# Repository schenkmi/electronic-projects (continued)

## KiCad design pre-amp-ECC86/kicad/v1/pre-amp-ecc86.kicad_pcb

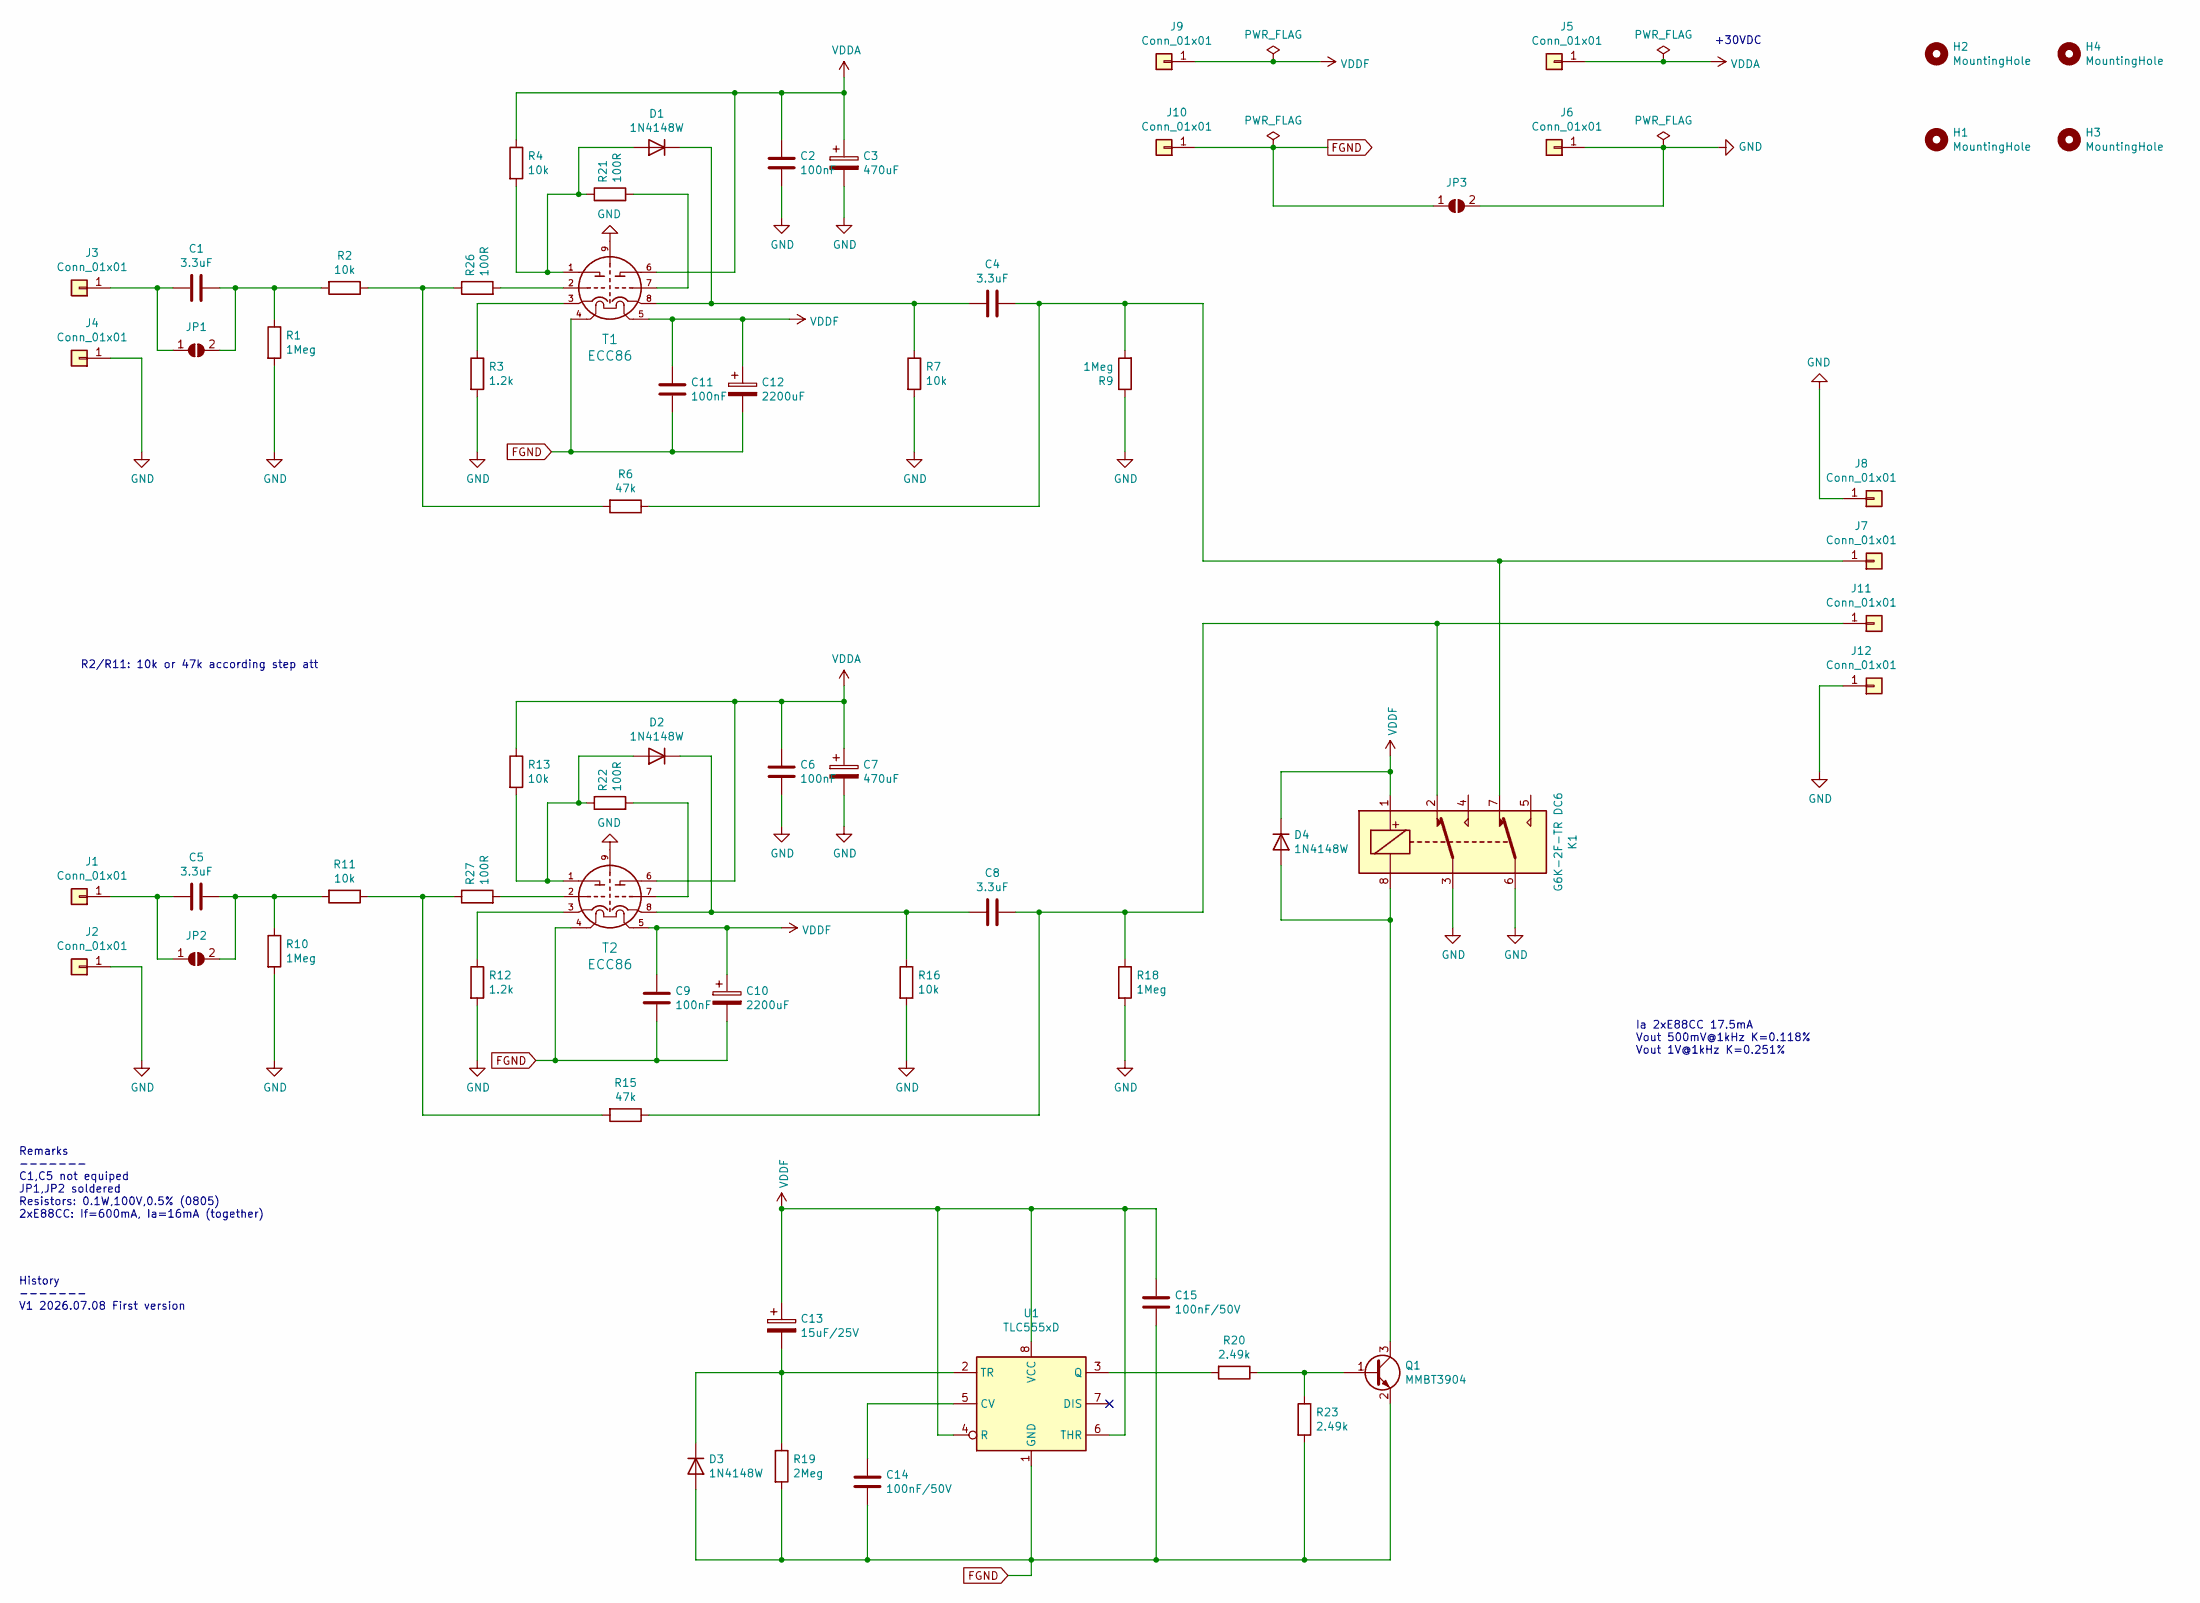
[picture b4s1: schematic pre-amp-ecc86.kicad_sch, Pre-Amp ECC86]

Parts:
C1, C4, C5, C8: 3.3uF; C_Rect_L7.2mm_W7.2mm_P5.00mm_FKS2_FKP2_MKS2_MKP2
C2, C6, C9, C11: 100nF; C_1206_3216Metric_Pad1.33x1.80mm_HandSolder
C3, C7: 470uF; CP_Radial_D12.5mm_P5.00mm
C10, C12: 2200uF; CP_Radial_D16.0mm_P7.50mm
C13: 15uF/25V; CP_EIA-3216-12_Kemet-S_HandSolder
C14, C15: 100nF/50V; C_0805_2012Metric_Pad1.18x1.45mm_HandSolder
D1, D2, D3, D4: 1N4148W; D_SOD-123
H1, H2, H3, H4: MountingHole; MountingHole_3.2mm_M3_Pad_Via
J1, J2, J3, J4, J7, J8, J11, J12: Conn_01x01; Pin_D1.0mm_L10.0mm
J5, J6, J9, J10: Conn_01x01; Pin_D1.3mm_L11.0mm
JP1, JP2, JP3: SolderJumper_2_Open; SolderJumper-2_P1.3mm_Open_Pad1.0x1.5mm
K1: G6K-2F-TR DC6; Relay_DPDT_Omron_G6K-2F
Q1: MMBT3904; SOT-23
R1, R9, R10, R18: 1Meg; R_0805_2012Metric_Pad1.20x1.40mm_HandSolder
R2, R4, R7, R11, R13, R16: 10k; R_0805_2012Metric_Pad1.20x1.40mm_HandSolder
R3, R12: 1.2k; R_0805_2012Metric_Pad1.20x1.40mm_HandSolder
R6, R15: 47k; R_0805_2012Metric_Pad1.20x1.40mm_HandSolder
R19: 2Meg; R_0805_2012Metric_Pad1.20x1.40mm_HandSolder
R20, R23: 2.49k; R_0805_2012Metric_Pad1.20x1.40mm_HandSolder
R21, R22, R26, R27: 100R; R_0805_2012Metric_Pad1.20x1.40mm_HandSolder
T1, T2: ECC86; TubeNoval-ECC86
U1: TLC555xD; SOIC-8_3.9x4.9mm_P1.27mm

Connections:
FGND: C9.2, C10.2, C11.2, C12.2, C14.2, C15.2, D3.2 (A), J10.1 (Pin_1_1), JP3.1 (A), Q1.2 (E), R19.2, R23.2, T1.4 (h), T2.4 (h), U1.1 (GND)
GND: C2.2, C3.2, C6.2, C7.2, J2.1 (Pin_1_1), J4.1 (Pin_1_1), J6.1 (Pin_1_1), J8.1 (Pin_1_1), J12.1 (Pin_1_1), JP3.2 (B), K1.3, K1.6, R1.2, R3.2, R7.2, R9.1, R10.2, R12.2, R16.2, R18.2, T1.9 (s), T2.9 (s)
unnamed: D1.2 (A), R4.2, R21.1, T1.1 (qT1)
unnamed: C4.2, D1.1 (K), R7.1, T1.8 (kT2)
unnamed: D2.2 (A), R13.2, R22.1, T2.1 (qT1)
unnamed: C8.2, D2.1 (K), R16.1, T2.8 (kT2)
unnamed: C13.2, D3.1 (K), R19.1, U1.2 (TR)
unnamed: D4.2 (A), K1.8, Q1.3 (C)
unnamed: C5.2, J1.1 (Pin_1_1), JP2.1 (A)
unnamed: C1.2, J3.1 (Pin_1_1), JP1.1 (A)
unnamed: C4.1, J7.1 (Pin_1_1), K1.7, R6.1, R9.2
unnamed: C8.1, J11.1 (Pin_1_1), K1.2, R15.1, R18.1
unnamed: C1.1, JP1.2 (B), R1.1, R2.2
unnamed: C5.1, JP2.2 (B), R10.1, R11.2
unnamed: Q1.1 (B), R20.1, R23.1
unnamed: R2.1, R6.2, R26.1
unnamed: R11.1, R15.2, R27.1
unnamed: R26.2, T1.2 (gT1)
unnamed: R21.2, T1.7 (gT2)
unnamed: R3.1, T1.3 (kT1)
unnamed: R27.2, T2.2 (gT1)
unnamed: R22.2, T2.7 (gT2)
unnamed: R12.1, T2.3 (kT1)
unnamed: C14.1, U1.5 (CV)
unnamed: R20.2, U1.3 (Q)
VDDA: C2.1, C3.1, C6.1, C7.1, J5.1 (Pin_1_1), R4.1, R13.1, T1.6 (qT2), T2.6 (qT2)
VDDF: C9.1, C10.1, C11.1, C12.1, C13.1, C15.1, D4.1 (K), J9.1 (Pin_1_1), K1.1, T1.5 (h), T2.5 (h), U1.4 (R), U1.6 (THR), U1.8 (VCC)

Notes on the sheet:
Remarks ------- C1,C5 not equiped JP1,JP2 soldered Resistors: 0.1W,100V,0.5% (0805) 2xE88CC: If=600mA, Ia=16mA (together)
R2/R11: 10k or 47k according step att
Ia 2xE88CC 17.5mA Vout 500mV@1kHz K=0.118% Vout 1V@1kHz K=0.251%
History ------- V1 2026.07.08 First version
+30VDC

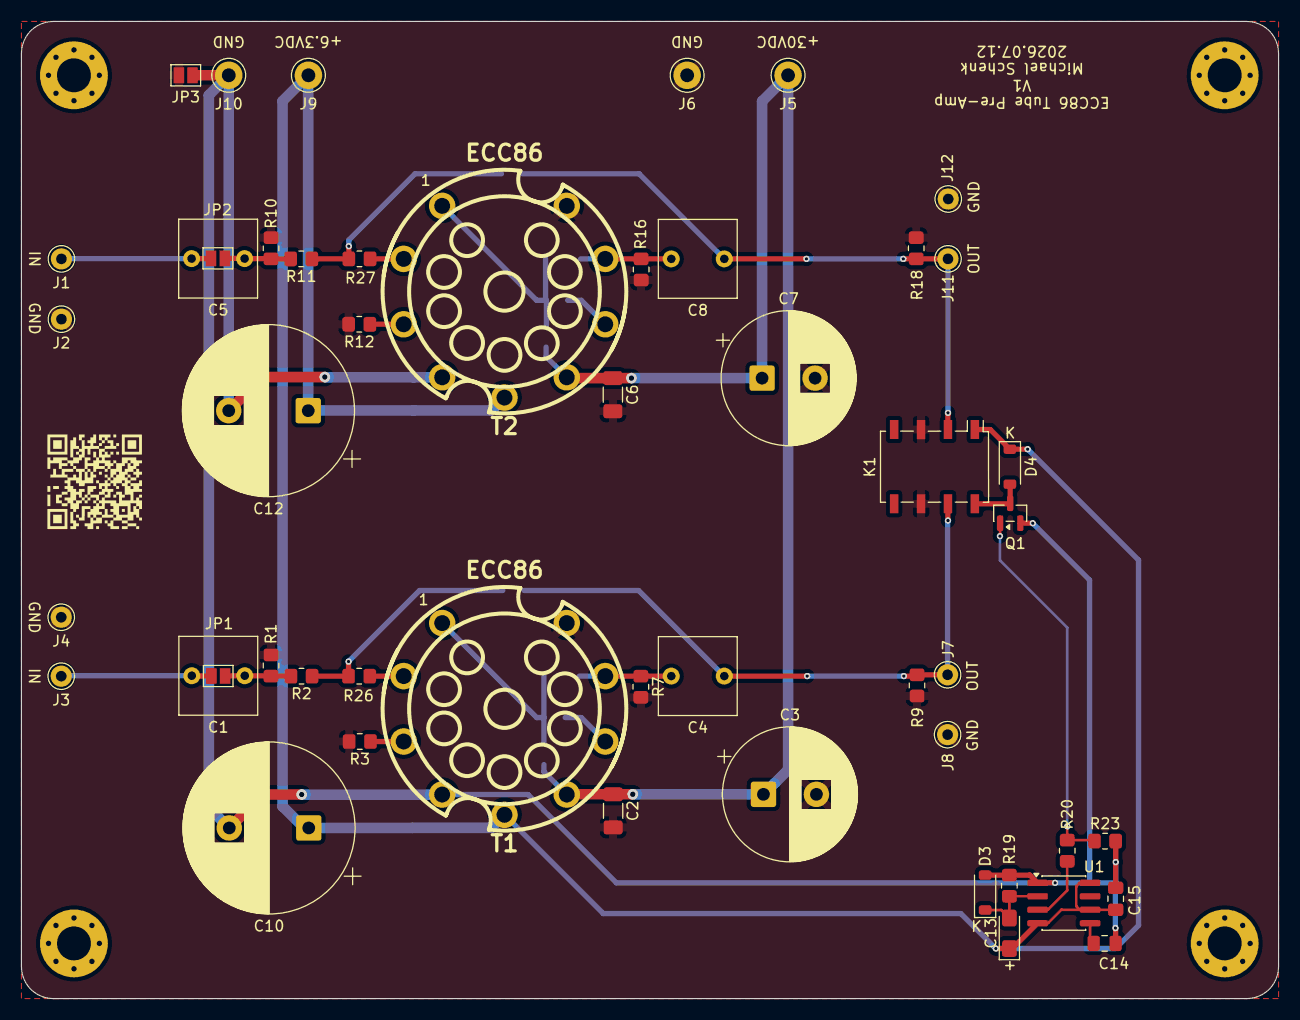
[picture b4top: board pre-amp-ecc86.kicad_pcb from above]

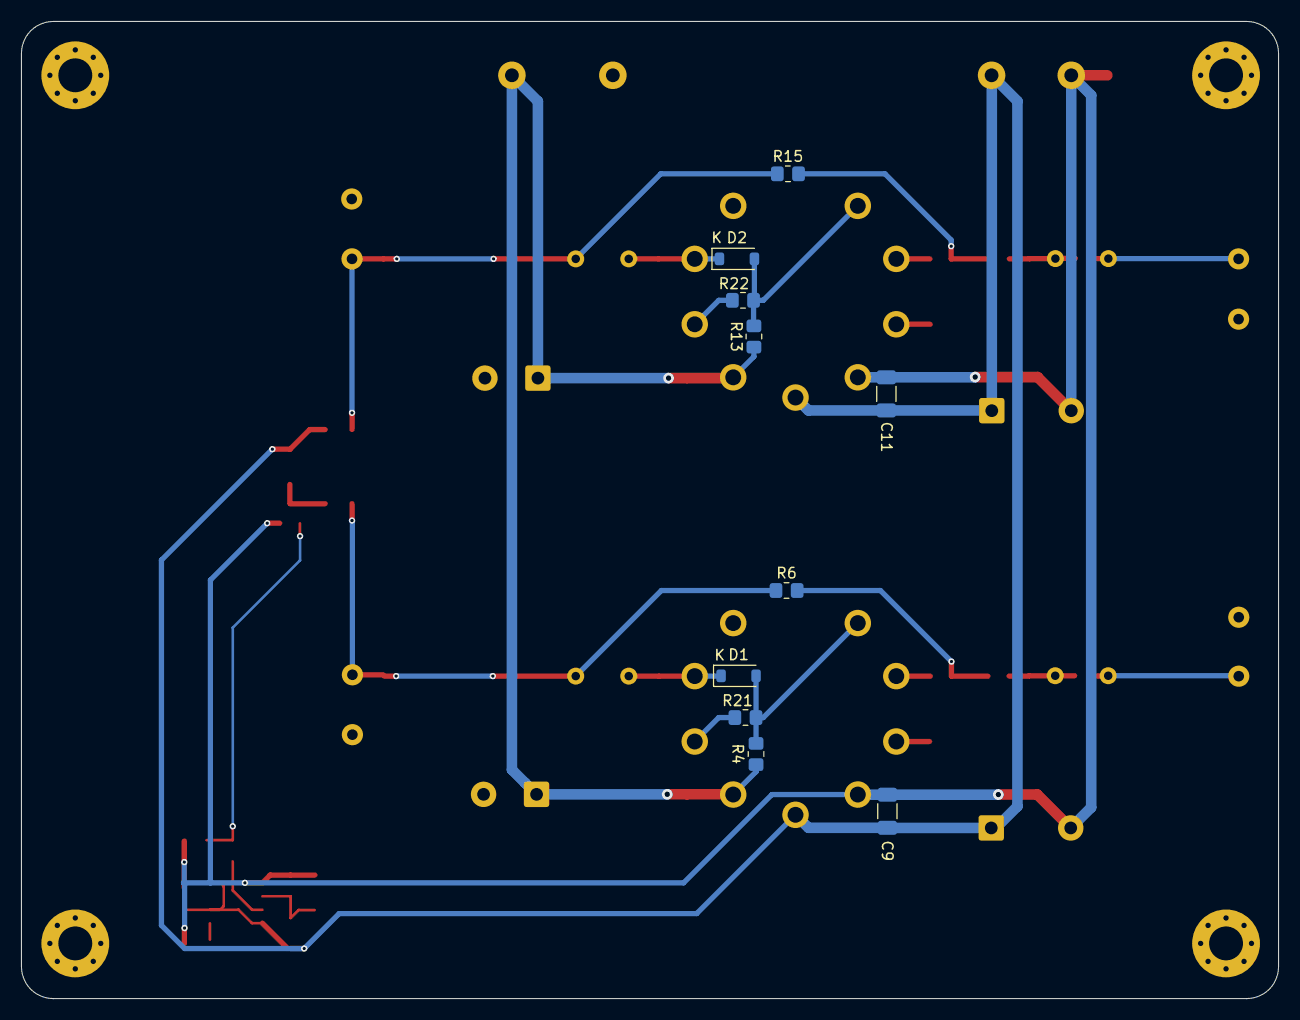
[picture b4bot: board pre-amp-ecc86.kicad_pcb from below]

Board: 2 copper layers, 118.6 x 92.2 mm, 64 parts (10 on the bottom side), 27 nets.

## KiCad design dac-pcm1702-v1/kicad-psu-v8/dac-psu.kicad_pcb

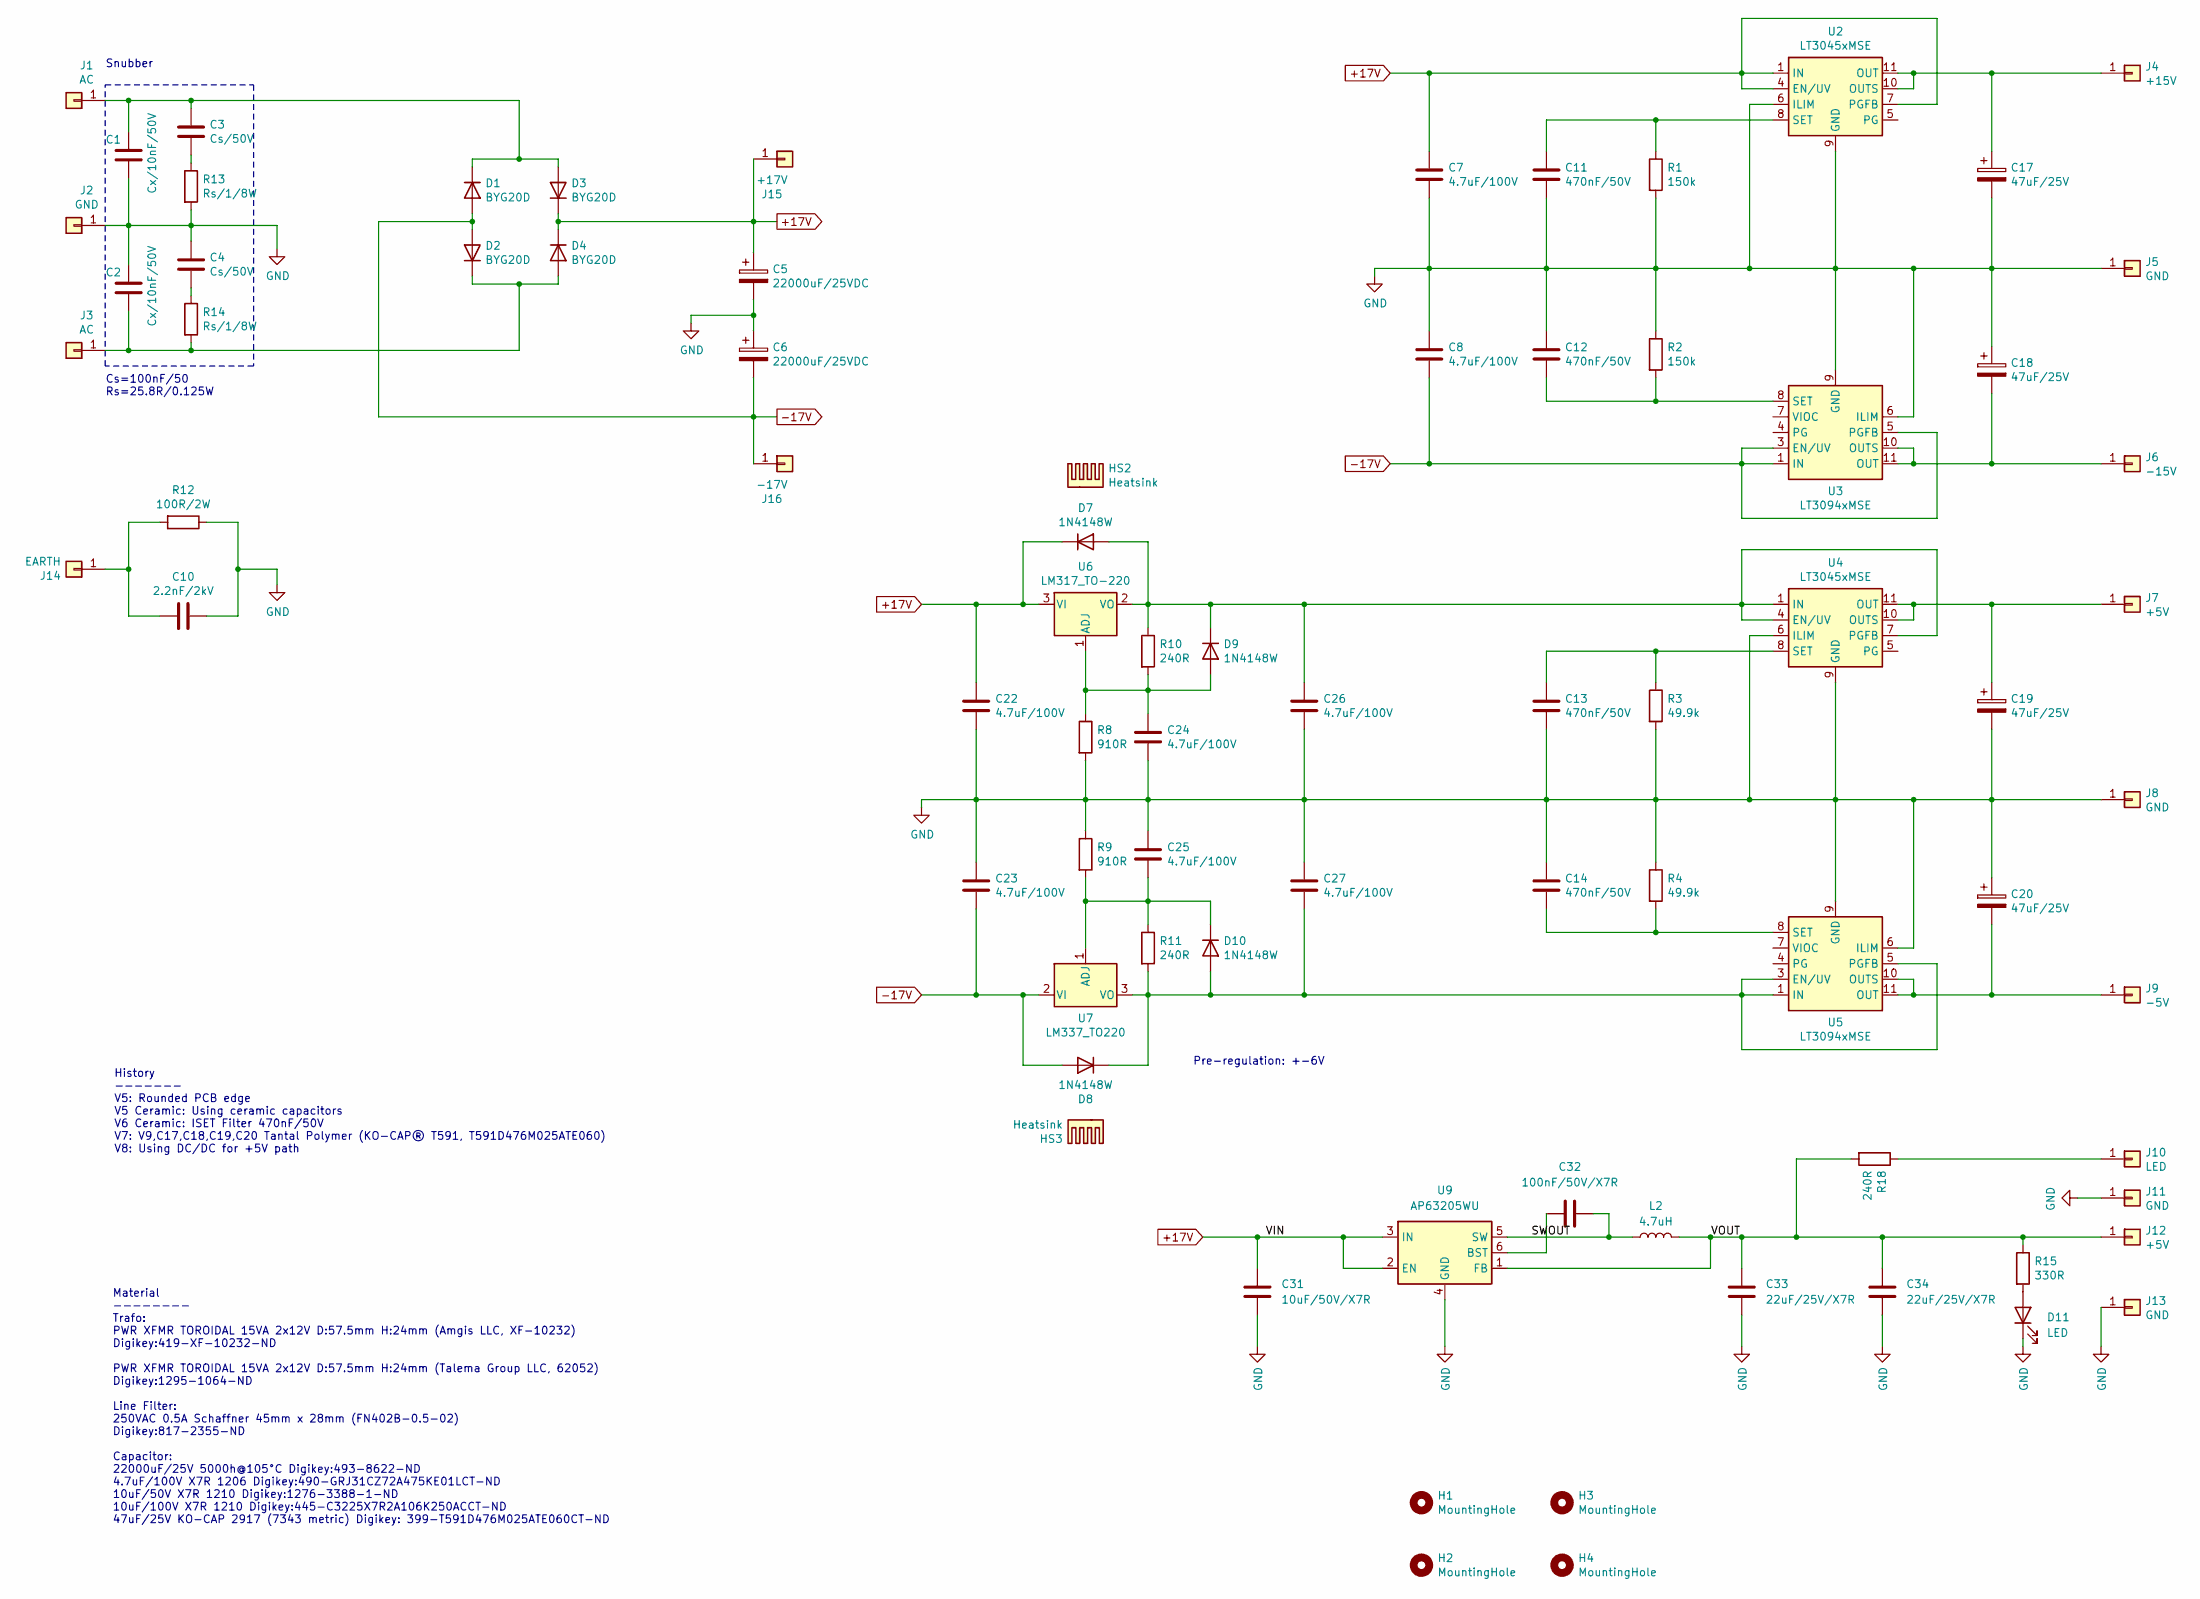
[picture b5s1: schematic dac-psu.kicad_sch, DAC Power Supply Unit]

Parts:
C1, C2: Cx/10nF/50V; C_0805_2012Metric_Pad1.18x1.45mm_HandSolder
C3, C4: Cs/50V; C_0805_2012Metric_Pad1.18x1.45mm_HandSolder
C5, C6: 22000uF/25VDC; CP_Radial_D35.0mm_P10.00mm_SnapIn
C7, C8, C22, C23, C24, C25, C26, C27: 4.7uF/100V; C_1206_3216Metric_Pad1.33x1.80mm_HandSolder
C10: 2.2nF/2kV; C_Rect_L18.0mm_W5.0mm_P15.00mm_FKS3_FKP3
C11, C12, C13, C14: 470nF/50V; C_0805_2012Metric_Pad1.18x1.45mm_HandSolder
C17, C18, C19, C20: 47uF/25V; CP_EIA-7343-31_Kemet-D_HandSolder
C31: 10uF/50V/X7R; C_1210_3225Metric_Pad1.33x2.70mm_HandSolder
C32: 100nF/50V/X7R; C_0805_2012Metric_Pad1.18x1.45mm_HandSolder
C33, C34: 22uF/25V/X7R; C_1210_3225Metric_Pad1.33x2.70mm_HandSolder
D1, D2, D3, D4: BYG20D; D_SMA_Handsoldering
D7, D8, D9, D10: 1N4148W; D_SOD-123
D11: LED; LED_0805_2012Metric_Pad1.15x1.40mm_HandSolder
H1, H2, H3, H4: MountingHole; MountingHole_3.2mm_M3_Pad_Via
HS2, HS3: Heatsink; Heatsink_Fischer_SK104-STC-STIC_35x13mm_2xDrill2.5mm
J1, J3: AC; Pin_D1.3mm_L11.0mm
J2: GND; Pin_D1.3mm_L11.0mm
J4: +15V; Pin_D1.0mm_L10.0mm
J5, J8, J11, J13: GND; Pin_D1.0mm_L10.0mm
J6: -15V; Pin_D1.0mm_L10.0mm
J7, J12: +5V; Pin_D1.0mm_L10.0mm
J9: -5V; Pin_D1.0mm_L10.0mm
J10: LED; Pin_D1.0mm_L10.0mm
J14: EARTH; Pin_D1.3mm_L11.0mm
J15: +17V; Pin_D1.3mm_L11.0mm
J16: -17V; Pin_D1.3mm_L11.0mm
L2: 4.7uH; L_Bourns_SRU5016_5.2x5.2mm
R1, R2: 150k; R_0603_1608Metric_Pad0.98x0.95mm_HandSolder
R3, R4: 49.9k; R_0603_1608Metric_Pad0.98x0.95mm_HandSolder
R8, R9: 910R; R_0603_1608Metric_Pad0.98x0.95mm_HandSolder
R10, R11: 240R; R_0603_1608Metric_Pad0.98x0.95mm_HandSolder
R12: 100R/2W; R_Axial_DIN0411_L9.9mm_D3.6mm_P15.24mm_Horizontal
R13, R14: Rs/1/8W; R_0805_2012Metric_Pad1.20x1.40mm_HandSolder
R15: 330R; R_0603_1608Metric_Pad0.98x0.95mm_HandSolder
R18: 240R; R_0805_2012Metric_Pad1.20x1.40mm_HandSolder
U2, U4: LT3045xMSE; MSOP-12-1EP_3x4.039mm_P0.65mm_EP1.651x2.845mm
U3, U5: LT3094xMSE; MSOP-12-1EP_3x4.039mm_P0.65mm_EP1.651x2.845mm
U6: LM317_TO-220; TO-220-3_Vertical
U7: LM337_TO220; TO-220-3_Vertical
U9: AP63205WU; TSOT-23-6

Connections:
+17V: C5.1, C7.1, C22.1, C31.1, D3.1 (K), D4.1 (K), D7.1 (K), J15.1 (Pin_1_1), U2.1 (IN), U2.2 (IN), U2.3 (IN), U2.4 (EN/UV), U2.7 (PGFB), U6.3 (VI), U9.2 (EN), U9.3 (IN)
-17V: C6.2, C8.2, C23.2, D1.2 (A), D2.2 (A), D8.2 (A), J16.1 (Pin_1_1), U3.1 (IN), U3.2 (IN), U3.3 (EN/UV), U3.5 (PGFB), U3.13 (IN), U7.2 (VI)
/SWOUT: C32.1, L2.1, U9.5 (SW)
/VOUT: C33.1, C34.1, J12.1 (Pin_1_1), L2.2, R15.1, R18.2, U9.1 (FB)
GND: C1.2, C2.1, C4.1, C5.2, C6.1, C7.2, C8.1, C10.1, C11.2, C12.1, C13.2, C14.1, C17.2, C18.1, C19.2, C20.1, C22.2, C23.1, C24.2, C25.1, C26.2, C27.1, C31.2, C33.2, C34.2, D11.1 (K), J2.1 (Pin_1_1), J5.1 (Pin_1_1), J8.1 (Pin_1_1), J11.1 (Pin_1_1), J13.1 (Pin_1_1), R1.2, R2.1, R3.2, R4.1, R8.2, R9.1, R12.1, R13.2, U2.6 (ILIM), U2.9 (GND), U2.13 (GND), U3.6 (ILIM), U3.9 (GND), U4.6 (ILIM), U4.9 (GND), U4.13 (GND), U5.6 (ILIM), U5.9 (GND), U9.4 (GND)
unnamed: C3.2, R13.1
unnamed: C4.2, R14.1
unnamed: C1.1, C3.1, D1.1 (K), D3.2 (A), J1.1 (Pin_1_1)
unnamed: C2.2, D2.1 (K), D4.2 (A), J3.1 (Pin_1_1), R14.2
unnamed: C26.1, D7.2 (A), D9.1 (K), R10.1, U4.1 (IN), U4.2 (IN), U4.3 (IN), U4.4 (EN/UV), U4.7 (PGFB), U6.2 (VO)
unnamed: C24.1, D9.2 (A), R8.1, R10.2, U6.1 (ADJ)
unnamed: C27.2, D8.1 (K), D10.2 (A), R11.2, U5.1 (IN), U5.2 (IN), U5.3 (EN/UV), U5.5 (PGFB), U5.13 (IN), U7.3 (VO)
unnamed: C25.2, D10.1 (K), R9.2, R11.1, U7.1 (ADJ)
unnamed: D11.2 (A), R15.2
unnamed: C17.1, J4.1 (Pin_1_1), U2.10 (OUTS), U2.11 (OUT), U2.12 (OUT)
unnamed: C18.2, J6.1 (Pin_1_1), U3.10 (OUTS), U3.11 (OUT), U3.12 (OUT)
unnamed: C19.1, J7.1 (Pin_1_1), U4.10 (OUTS), U4.11 (OUT), U4.12 (OUT)
unnamed: C20.2, J9.1 (Pin_1_1), U5.10 (OUTS), U5.11 (OUT), U5.12 (OUT)
unnamed: J10.1 (Pin_1_1), R18.1
unnamed: C10.2, J14.1 (Pin_1_1), R12.2
unnamed: C11.1, R1.1, U2.8 (SET)
unnamed: C12.2, R2.2, U3.8 (SET)
unnamed: C13.1, R3.1, U4.8 (SET)
unnamed: C14.2, R4.2, U5.8 (SET)
unnamed: C32.2, U9.6 (BST)

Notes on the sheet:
Material -------- Trafo: PWR XFMR TOROIDAL 15VA 2x12V D:57.5mm H:24mm (Amgis LLC, XF-10232) Digikey:419-XF-10232-ND PWR XFMR TOROIDAL 15VA 2x12V D:57.5mm H:24mm (Talema Group LLC, 62052) Digikey:1295-1064-ND Line Filter: 250VAC 0.5A Schaffner 45mm x 28mm (FN402B-0.5-02) Digikey:817-2355-ND Capacito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
Snubber
Cs=100nF/50 Rs=25.8R/0.125W
Pre-regulation: +-6V
History ------- V5: Rounded PCB edge V5 Ceramic: Using ceramic capacitors V6 Ceramic: ISET Filter 470nF/50V V7: V9,C17,C18,C19,C20 Tantal Polymer (KO-CAP® T591, T591D476M025ATE060) V8: Using DC/DC for +5V path

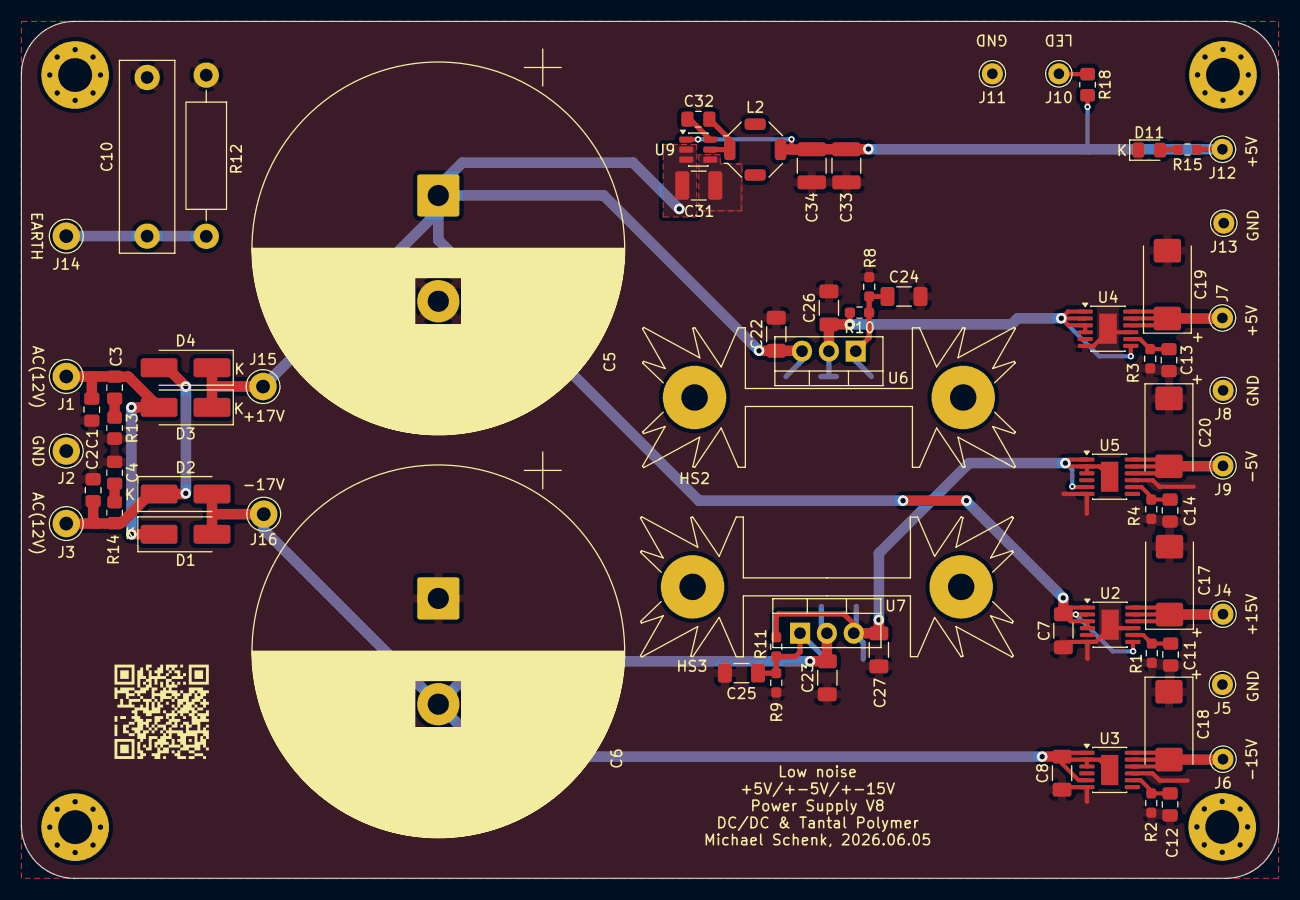
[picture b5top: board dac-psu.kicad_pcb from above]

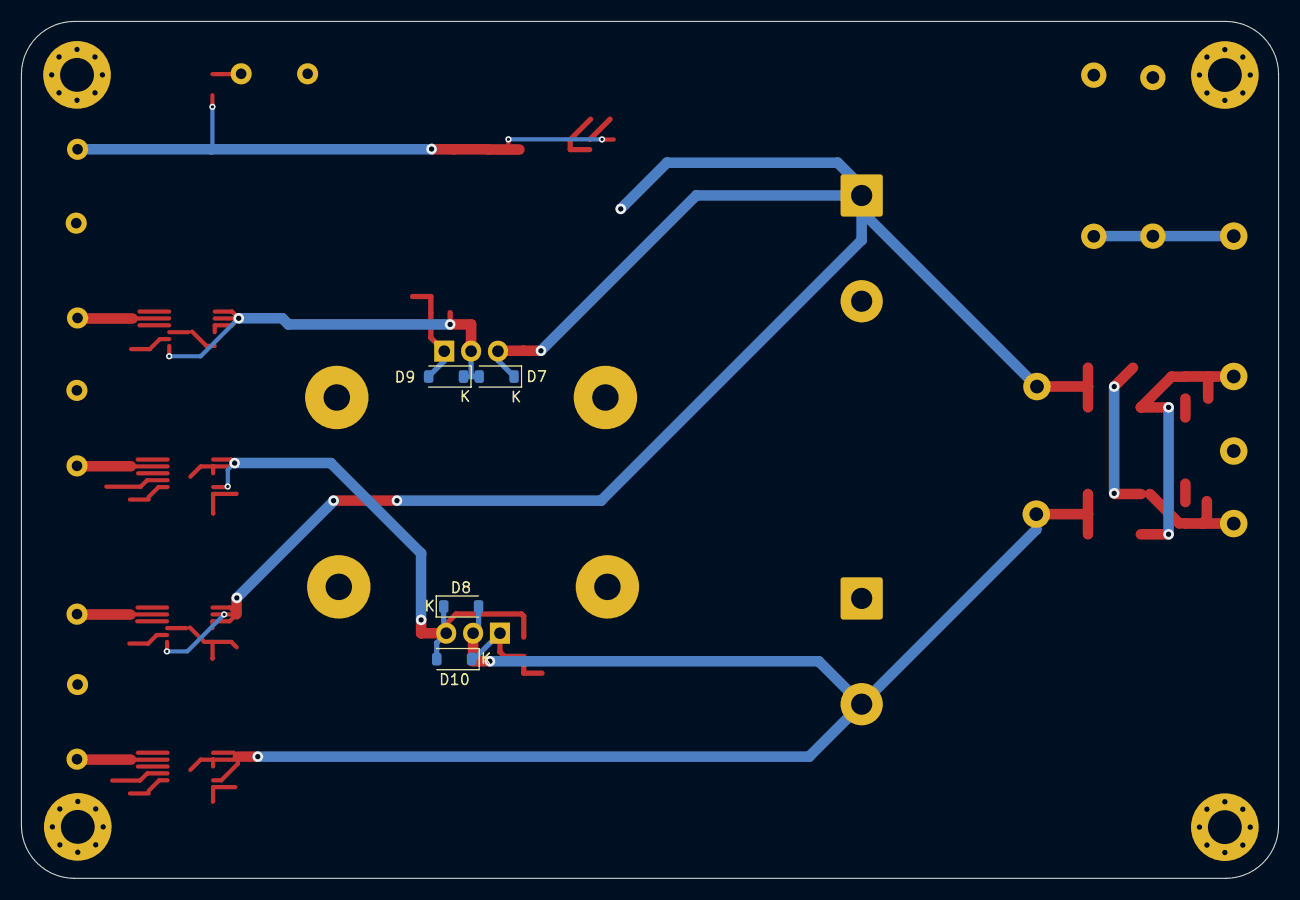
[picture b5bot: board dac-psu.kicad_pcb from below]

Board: 2 copper layers, 118.9 x 81.0 mm, 79 parts (4 on the bottom side), 25 nets.
